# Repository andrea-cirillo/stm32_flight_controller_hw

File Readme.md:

<p align="center">
  <picture>
    <source media="(prefers-color-scheme: dark)" srcset="00%20-%20Docs/05%20-%20Brand/ACwing_logo_white.png">
    
  </picture>
</p>

<h1 align="center">ACwing – open drone flight hardware</h1>

<p align="center">
  STM32WB55 flight controller, 1S power board, GNSS and optical-flow expansions<br>
  KiCad 7 · JLCPCB-ready · by Andrea Cirillo
</p>

---

ACwing is a modular set of PCBs for small multirotors. The core is a **universal flight controller** that talks to its
power stage through the common **4-in-1 ESC connector** (JST SH 8-pin): on the 1S indoor mini drone it sits on the
ACwing 1S power board; on a larger 3S–6S brushless drone the same FC runs with one or two commercial 20 × 20 4-in-1
ESCs. Two optional expansion boards plug into the FC's **Qwiic** (I2C) ports: a **GNSS + compass** board for outdoor
flight and an **optical-flow + ToF** board for indoor position and height hold.

## Boards

| Board | Rev | Size | Layers | What it does | Docs | KiCad |
|---|---|---|---|---|---|---|
| **ACwing FC** | H | 40 × 40 mm, 20 × 20 holes (grommets) | 4, 1.0 mm | flight controller, 1S–6S input, up to 8 motors, BLE | [FC docs](00%20-%20Docs/00%20-%20FC_Docs/) | [project](01%20-%20FC_KiCadProj/) |
| **ACwing ESC 1S** | B | 40 × 40 mm, 20 × 20 holes | 4, 1.0 mm | 1S power board: 4 brushed motor stages, current sensor, USB-C charger | [ESC docs](00%20-%20Docs/01%20-%20ESC_1S_Docs/) | [project](02%20-%20ESC_1S_KiCadProj/) |
| **ACwing GPS** | D | 30 × 30 mm, 20 × 20 holes | 2, 1.0 mm | GNSS (u-blox SAM-M10Q) + compass, stacked above the FC | [GPS docs](00%20-%20Docs/02%20-%20GPS_Docs/) | [project](03%20-%20GPS_KiCadProj/) |
| **ACwing Flow** | A | 21 × 25 mm, 2 × M2 | 2, 1.0 mm | optical flow (PMW3901) + ToF height (VL53L1X), under the frame | [Flow docs](00%20-%20Docs/03%20-%20FLOW_Docs/) | [project](04%20-%20FLOW_KiCadProj/) |

Every board folder in `00 - Docs` holds the schematic PDF, the BoM with costing, the JLCPCB BoM and pick-and-place
files, the Gerber zip, the DRC report, the STEP model and board views.

## System

```
              ┌─────────────────────────┐   Qwiic (J3)   ┌──────────────────┐
              │      ACwing FC rev A    │───────────────▶│  ACwing GPS rev A │  optional, outdoor
  USB-C ─────▶│ STM32WB55 · IMU · baro  │                └──────────────────┘
  ELRS RX ───▶│ compass · 16 MB flash   │   Qwiic (J4)   ┌──────────────────┐
              │ BLE · 4 × RGB LED       │───────────────▶│ ACwing Flow rev A │  indoor
              └───────┬─────────┬───────┘                └──────────────────┘
          ESC link A  │         │  ESC link B (motors 5–8)
         (JST SH 8)   ▼         ▼
   ┌──────────────────────┐   ┌──────────────────────────┐
   │ ACwing ESC 1S rev A  │ or│ commercial 4-in-1 ESC(s) │
   │ 1S, brushed, charger │   │ 2S–6S, brushless         │
   └──────────────────────┘   └──────────────────────────┘
```

**Stack (1S mini drone, frame C2):** ESC 1S hard-mounted on the frame bosses → 5 mm → FC on M2 damping grommets →
6 mm → GPS board (optional). The flow board is mounted under the battery bay, sensor side down.

The interactive stack check (every part as a prism, every connector with a mated-plug envelope; 0 clashes) is in
[`04 - System_Docs/ACwing_stack_check.html`](00%20-%20Docs/04%20-%20System_Docs/) – download the folder and open the
page locally.

## Key features

**ACwing FC rev A**
- MCU **STM32WB55CGU6** (Cortex-M4 + M0+ radio core), BLE 5 with chip antenna and ST MLPF-WB55 front end.
- Sensors: **LSM6DSV16X** IMU, **LPS22HB** barometer, **IIS2MDC** compass; **W25Q128JV** 16 MB log flash.
- Input **1S–6S** (LM5166 buck, 3–65 V; 100 % duty cycle pass-through on 1S), 4.1 V system rail, 3.1 V and 3.31 V LDOs.
- **Two ESC links** (JST SH 8-pin, standard 4-in-1 pinout): 8 motor outputs (TIM2 / TIM1 / TIM16), VBAT and current
  sense from the ESC, battery pads for setups without a VBAT pin.
- Two Qwiic ports, ELRS / CRSF UART port, USB-C (data, DFU, bench supply), 4 × WS2812B, SWD pogo grid.

**ACwing ESC 1S rev A**
- 4 brushed motor stages (AON7524 N-MOSFETs) for coreless 8520 motors, 470 µF bulk capacitor.
- 2 mΩ shunt + TSC213 current sense (0.1 V/A) on the ESC link.
- USB-C 1S charger (STC4054, 455 mA) with a charge switch that keeps FC and motors off while charging.
- Battery solder pads for a JST PH 2.0 pigtail.

**ACwing GPS rev A** – u-blox **SAM-M10Q** (integrated patch antenna, I2C/DDC) and **IIS2MDC** compass away from the
motor currents; Qwiic in / out on the top side, PPS LED, backup supply.

**ACwing Flow rev A** – PixArt **PMW3901MB** flow sensor behind an **STM32C011** I2C bridge, ST **VL53L1X** ToF;
Qwiic in / out; all parts on the sensor side.

## Repository structure

```
00 - Docs/
├── 00 - FC_Docs/         FC rev A: README, pin map, schematic, BoM, JLC files, Gerber, STEP, views
├── 01 - ESC_1S_Docs/     ESC 1S rev A: same set
├── 02 - GPS_Docs/        GPS rev A: same set
├── 03 - FLOW_Docs/       Flow rev A: same set + mechanical DXF
├── 04 - System_Docs/     mechanical handoff, frame C2 answer and reply, stack check (3D page and render)
└── 05 - Brand/           ACwing logos (SVG/PNG), silkscreen logo footprints, brand and silkscreen tools
01 - FC_KiCadProj/        KiCad project, library, 3D models, generator scripts
02 - ESC_1S_KiCadProj/
03 - GPS_KiCadProj/
04 - FLOW_KiCadProj/
```

## Ordering (JLCPCB)

For each board, from its docs folder:
1. Upload `<board>_gerber.zip` (1.0 mm FR-4; 4 layers for FC and ESC, 2 layers for GPS and Flow).
2. Enable assembly and upload `<board>_BoM_JLCPCB.xlsx` and `<board>_CPL.xlsx`. Every BoM line carries its LCSC part
   number; the CPL already includes the rotation corrections. Check the pin-1 marks in the JLC preview as listed in the
   board README ("To check before ordering").

Indicative component cost per board (10 / 100 boards, components only): FC 28.2 / 22.7 USD, ESC 1S 6.4 / 5.1 USD,
GPS 27.6 / 23.4 USD, Flow 11.1 / 9.4 USD. Check LCSC stock before ordering.

## Status

**Layout update 2026-10-24 (still rev A):** FC microcontroller at the board centre, ESC link B next to the ELRS port on
the front edge, input buck moved to the left edge (no longer between the rear LEDs), LED supply kept away from the
magnetometer (EMI check in the FC README); GPS Qwiic J1 aligned with FC J3.

All four boards are routed with **0 DRC violations and 0 unconnected pads** (KiCad 7.0). They are not built and tested
yet: see each board README for the bench checks planned before the first order (ERC in KiCad 8/9, power-stage tests,
land patterns to verify). Firmware is a separate project.

## Author

**Andrea Cirillo** – ACwing hardware design.

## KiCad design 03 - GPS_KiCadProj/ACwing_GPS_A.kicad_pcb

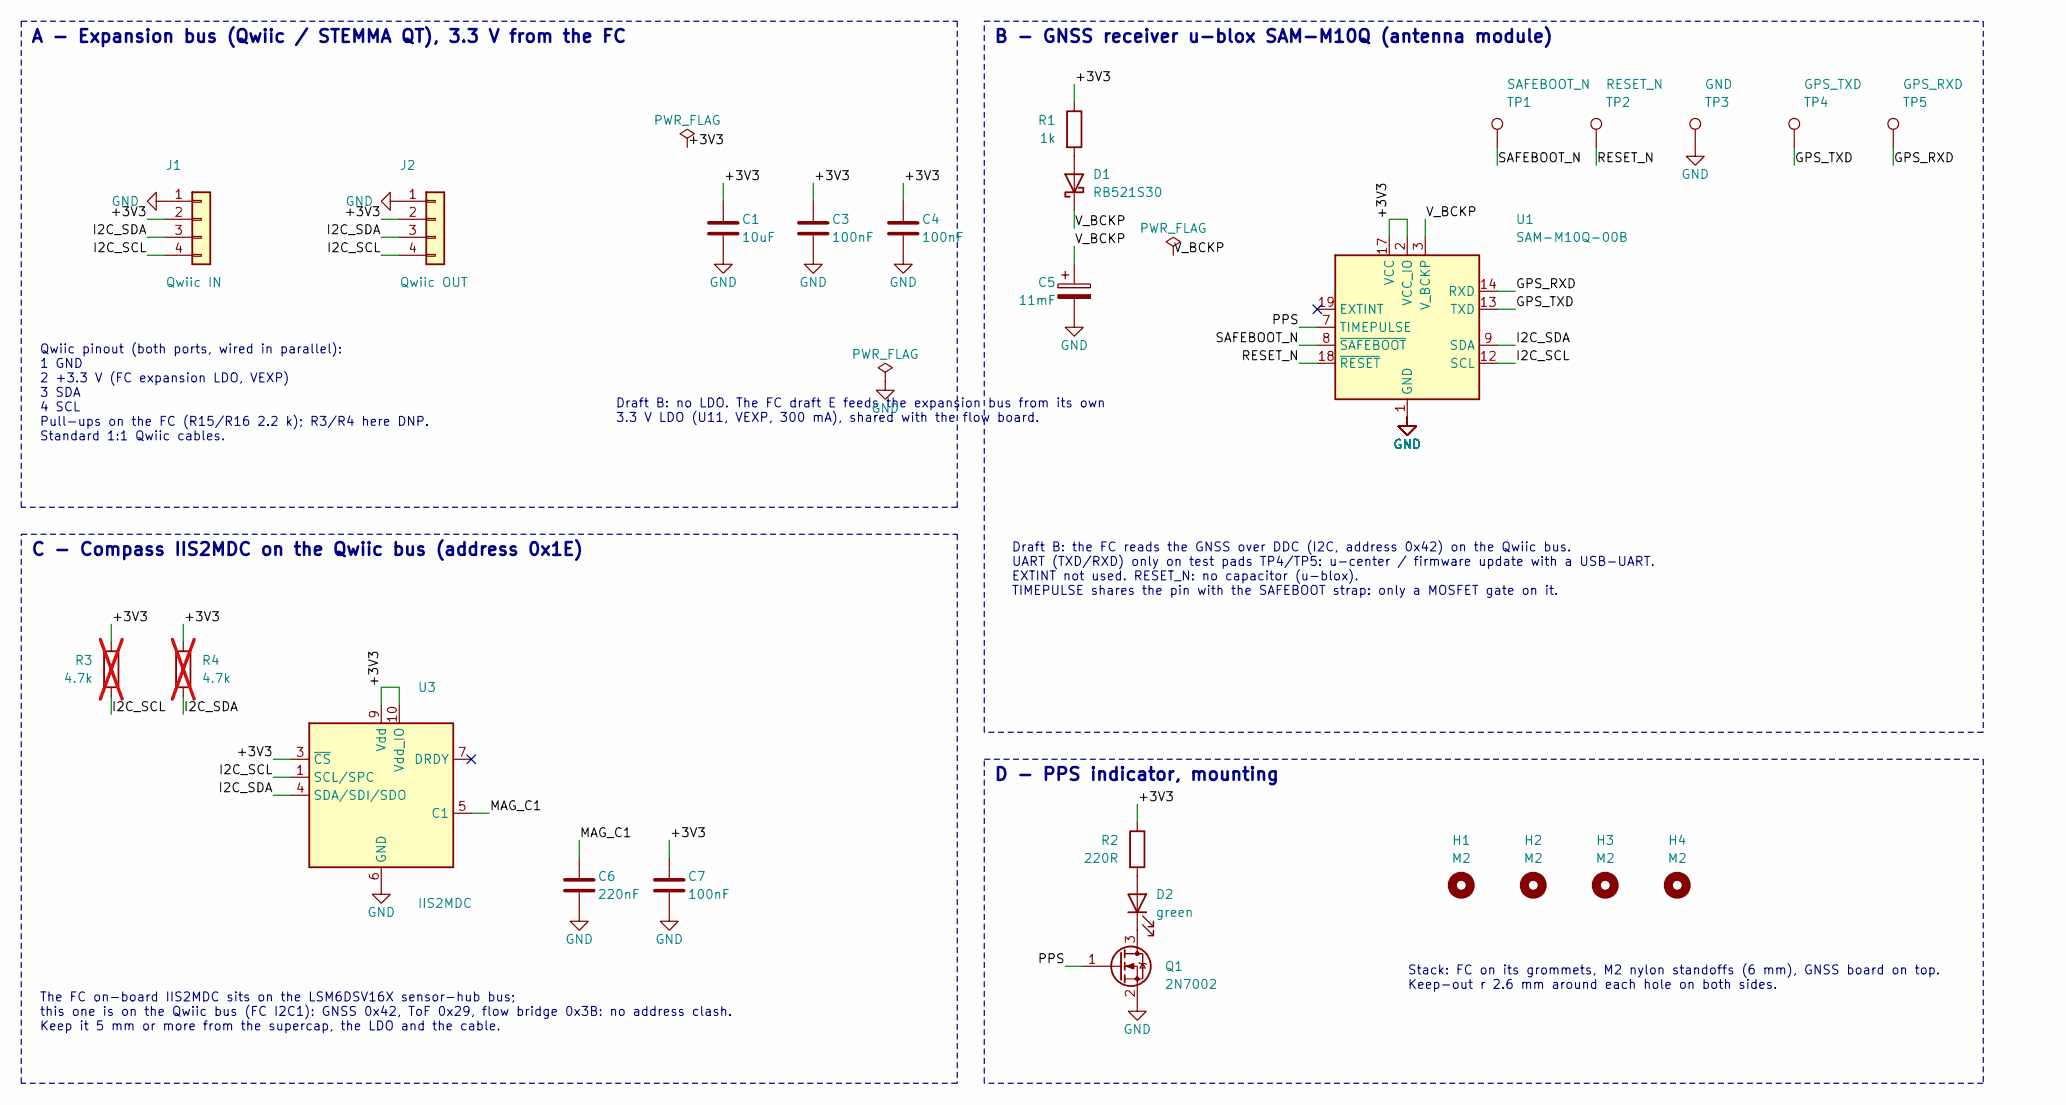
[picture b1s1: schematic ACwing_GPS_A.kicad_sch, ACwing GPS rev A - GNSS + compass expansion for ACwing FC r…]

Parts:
C1: 10uF; C_0603_1608Metric
C3, C4, C7: 100nF; C_0402_1005Metric
C5: 11mF; C_1210_3225Metric
C6: 220nF; C_0402_1005Metric
D1: RB521S30; D_SOD-523
D2: green; LED_0402_1005Metric
H1, H2, H3, H4: M2; MountingHole_2.2mm_M2
J1: Qwiic IN; JST_SH_SM04B-SRSS-TB_1x04-1MP_P1.00mm_Horizontal
J2: Qwiic OUT; JST_SH_SM04B-SRSS-TB_1x04-1MP_P1.00mm_Horizontal
Q1: 2N7002; SOT-23
R1: 1k; R_0402_1005Metric
R2: 220R; R_0402_1005Metric
R3, R4: 4.7k; R_0402_1005Metric; not fitted
TP1: SAFEBOOT_N; TestPoint_Pad_D1.0mm
TP2: RESET_N; TestPoint_Pad_D1.0mm
TP3: GND; TestPoint_Pad_D1.0mm
TP4: GPS_TXD; TestPoint_Pad_D1.0mm
TP5: GPS_RXD; TestPoint_Pad_D1.0mm
U1: SAM-M10Q-00B; ublox_SAM-M8Q
U3: IIS2MDC; LGA-12_2x2mm_P0.5mm

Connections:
+3V3: C1.1, C3.1, C4.1, C7.1, J1.2, J2.2, R1.1, R2.1, R3.1, R4.1, U1.2 (VCC_IO), U1.17 (VCC), U3.3 (~CS), U3.9 (Vdd), U3.10 (Vdd_IO)
GND: C1.2, C3.2, C4.2, C5.2, C6.2, C7.2, J1.1, J2.1, Q1.2 (S), TP3.1, U1.1 (GND), U1.4 (GND), U1.5 (GND), U1.6 (GND), U1.10 (GND), U1.11 (GND), U1.15 (GND), U1.16 (GND), U1.20 (GND), U3.6 (GND), U3.8 (GND)
GPS_RXD: TP5.1, U1.14 (RXD)
GPS_TXD: TP4.1, U1.13 (TXD)
I2C_SCL: J1.4, J2.4, R3.2, U1.12 (SCL), U3.1 (SCL/SPC)
I2C_SDA: J1.3, J2.3, R4.2, U1.9 (SDA), U3.4 (SDA/SDI/SDO)
MAG_C1: C6.1, U3.5 (C1)
unnamed: D1.2 (A), R1.2
unnamed: D2.2 (A), R2.2
unnamed: D2.1 (K), Q1.3 (D)
PPS: Q1.1 (G), U1.7 (TIMEPULSE)
RESET_N: TP2.1, U1.18 (~RESET)
SAFEBOOT_N: TP1.1, U1.8 (~SAFEBOOT)
V_BCKP: C5.1, D1.1 (K), U1.3 (V_BCKP)

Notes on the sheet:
A - Expansion bus (Qwiic / STEMMA QT), 3.3 V from the FC
Qwiic pinout (both ports, wired in parallel): 1 GND 2 +3.3 V (FC expansion LDO, VEXP) 3 SDA 4 SCL Pull-ups on the FC (R15/R16 2.2 k); R3/R4 here DNP. Standard 1:1 Qwiic cables.
Draft B: no LDO. The FC draft E feeds the expansion bus from its own 3.3 V LDO (U11, VEXP, 300 mA), shared with the flow board.
B - GNSS receiver u-blox SAM-M10Q (antenna module)
Draft B: the FC reads the GNSS over DDC (I2C, address 0x42) on the Qwiic bus. UART (TXD/RXD) only on test pads TP4/TP5: u-center / firmware update with a USB-UART. EXTINT not used. RESET_N: no capacitor (u-blox). TIMEPULSE shares the pin with the SAFEBOOT strap: only a MOSFET gate on it.
C - Compass IIS2MDC on the Qwiic bus (address 0x1E)
The FC on-board IIS2MDC sits on the LSM6DSV16X sensor-hub bus; this one is on the Qwiic bus (FC I2C1): GNSS 0x42, ToF 0x29, flow bridge 0x3B: no address clash. Keep it 5 mm or more from the supercap, the LDO and the cable.
D - PPS indicator, mounting
Stack: FC on its grommets, M2 nylon standoffs (6 mm), GNSS board on top. Keep-out r 2.6 mm around each hole on both sides.

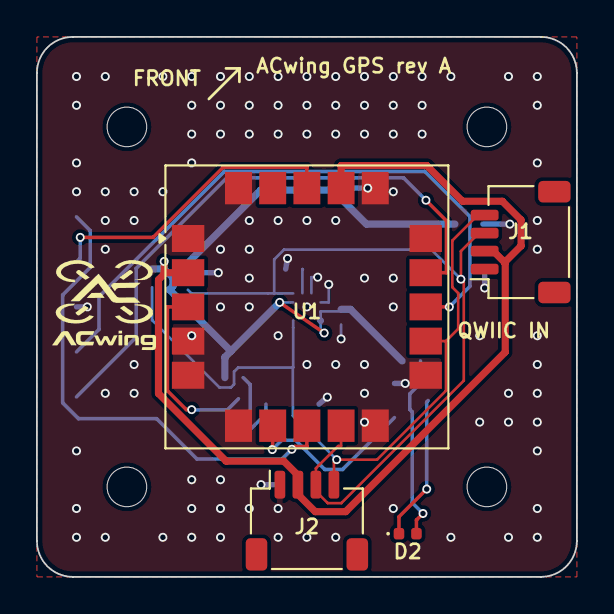
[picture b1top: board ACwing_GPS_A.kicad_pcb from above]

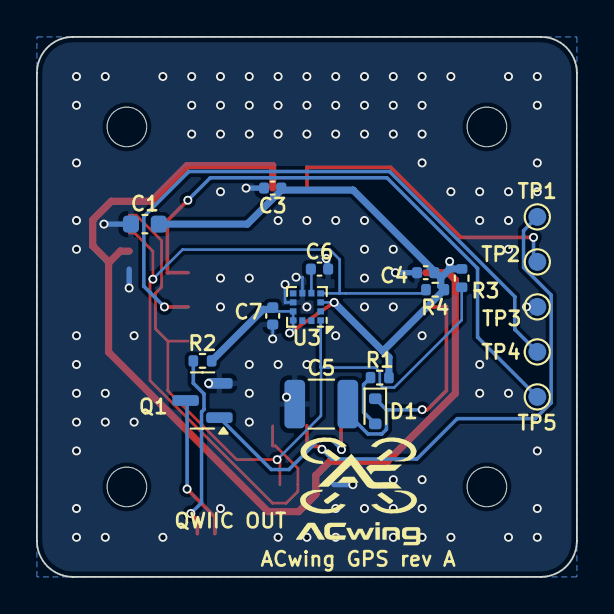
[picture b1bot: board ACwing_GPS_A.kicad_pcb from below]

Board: 2 copper layers, 30.0 x 30.0 mm, 28 parts (19 on the bottom side), 14 nets.

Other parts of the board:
LOGO1: ACwing_Logo_Full_5mm
LOGO2: ACwing_Logo_Full_6mm

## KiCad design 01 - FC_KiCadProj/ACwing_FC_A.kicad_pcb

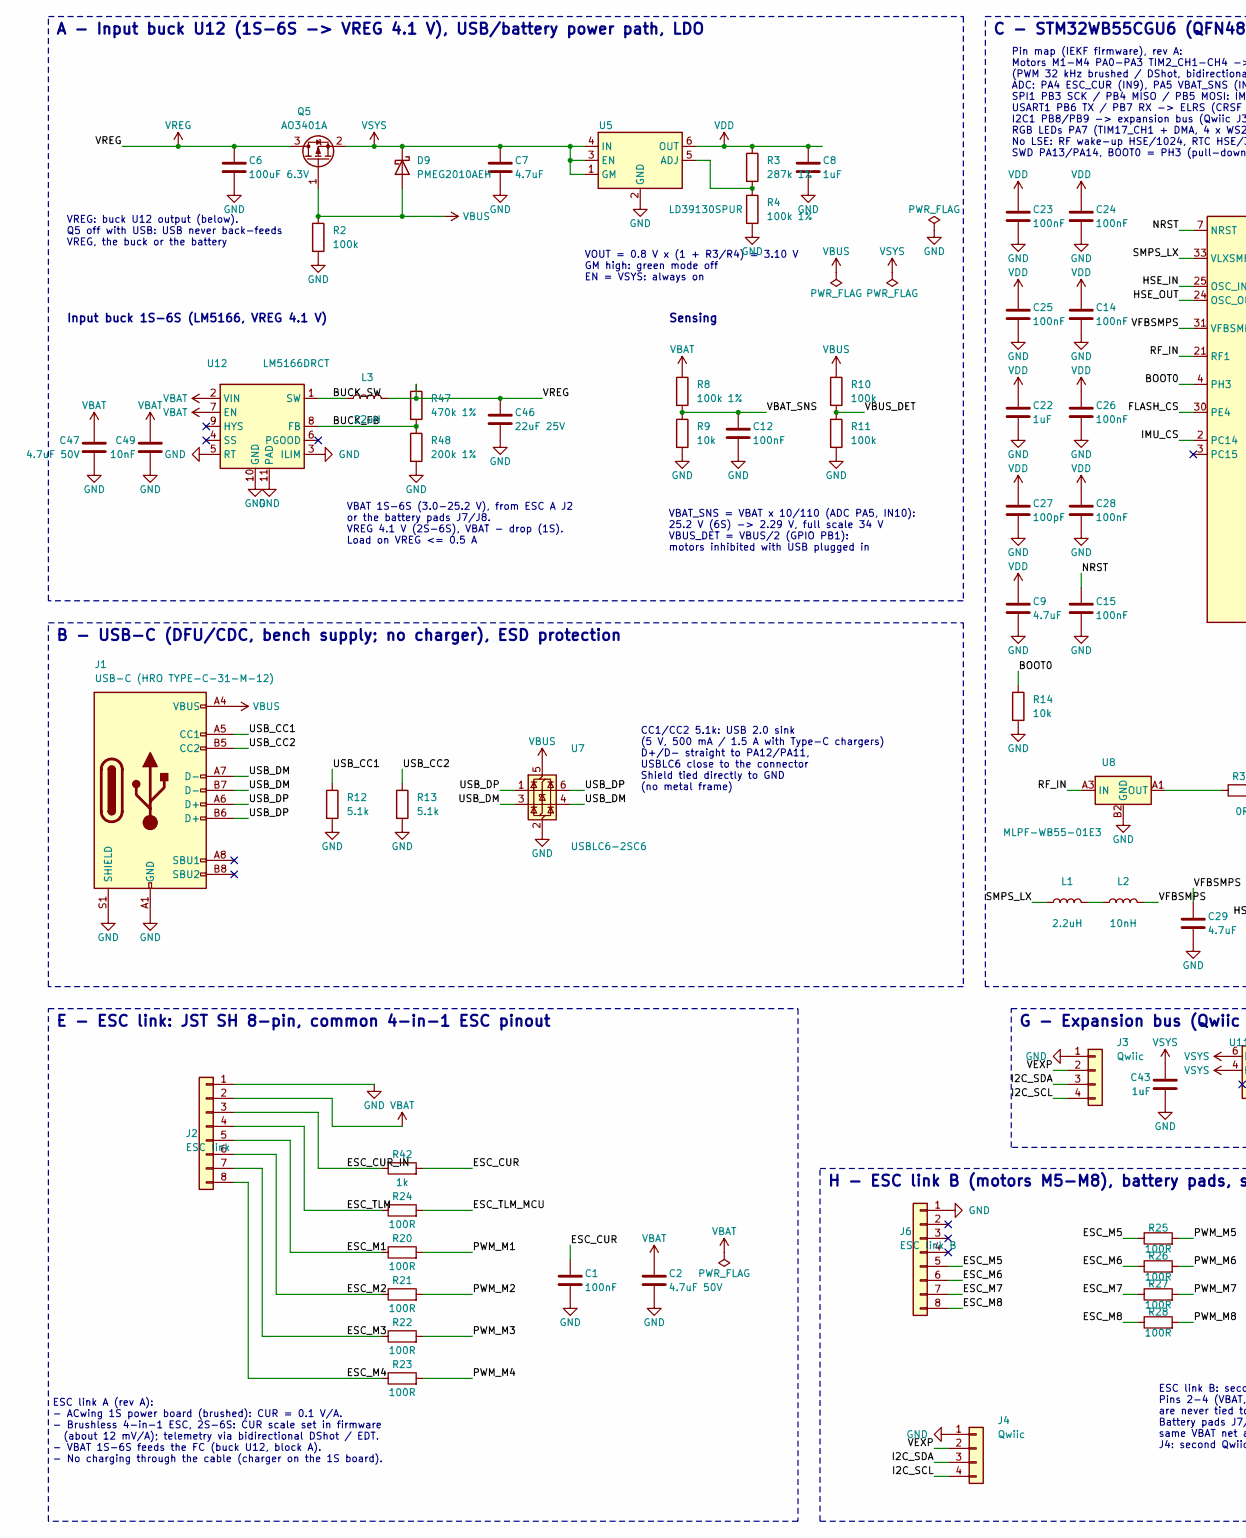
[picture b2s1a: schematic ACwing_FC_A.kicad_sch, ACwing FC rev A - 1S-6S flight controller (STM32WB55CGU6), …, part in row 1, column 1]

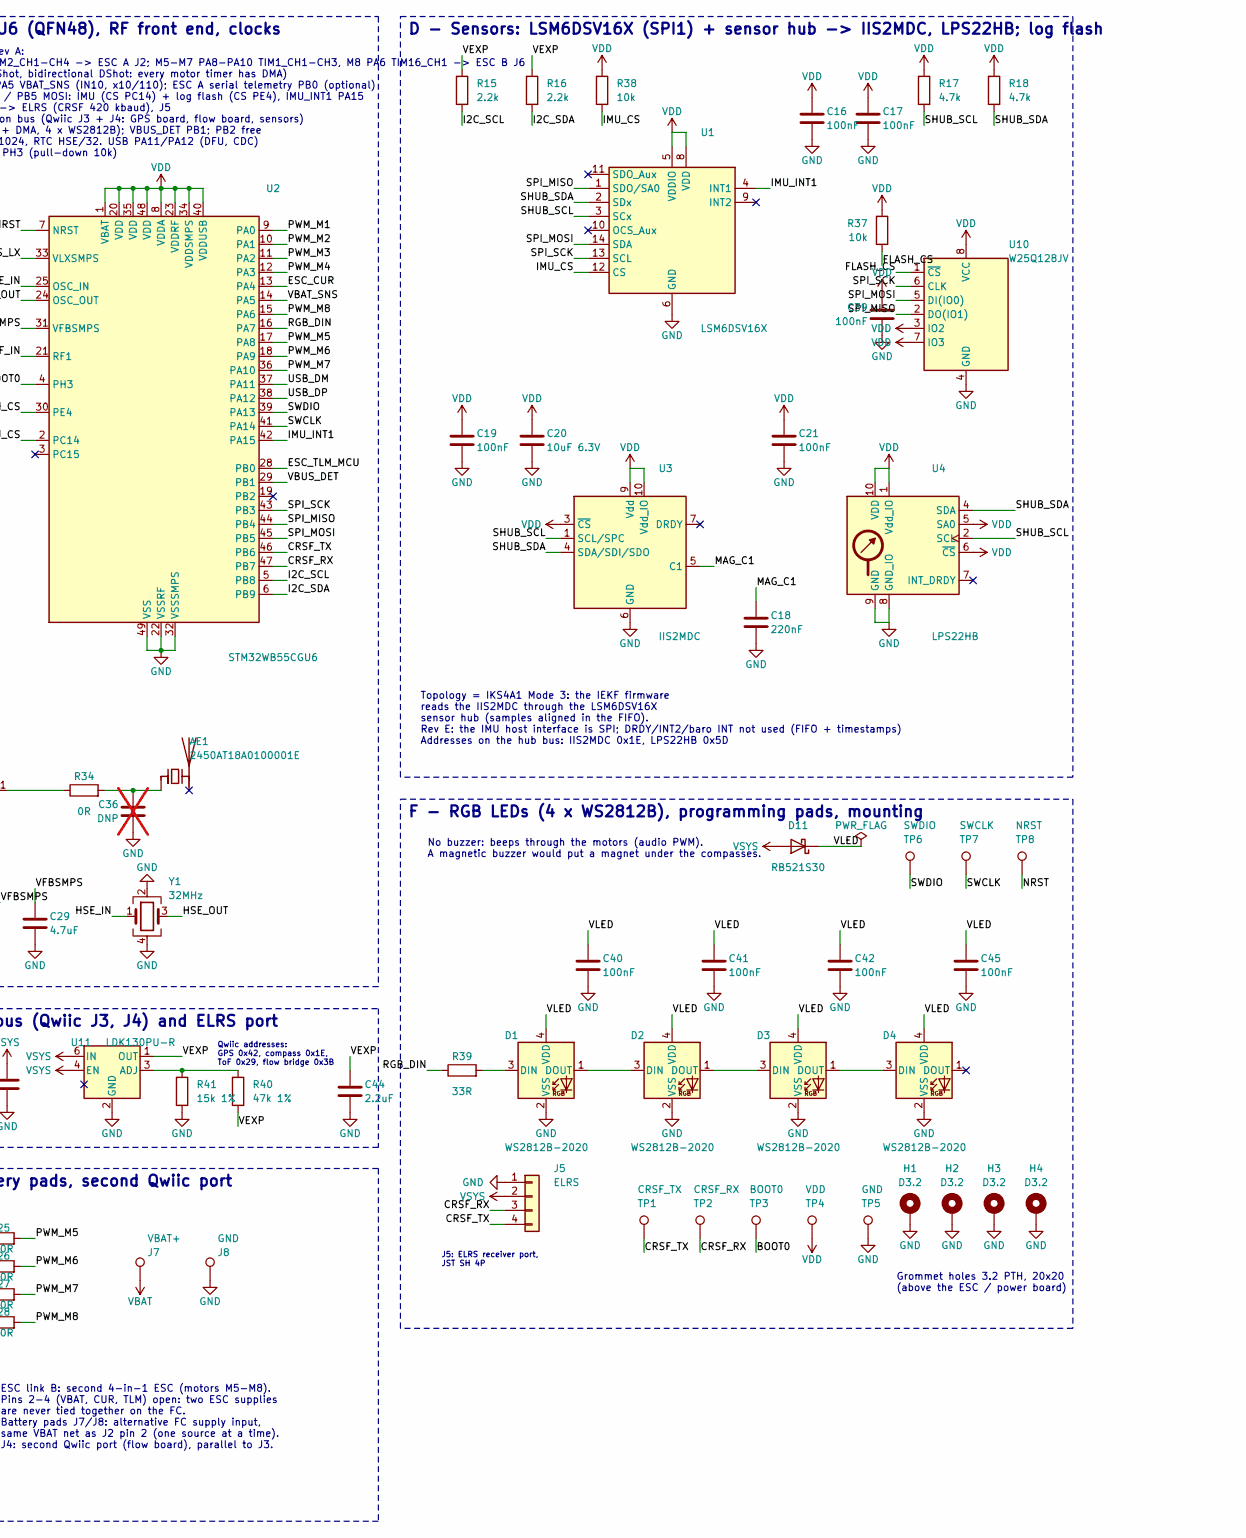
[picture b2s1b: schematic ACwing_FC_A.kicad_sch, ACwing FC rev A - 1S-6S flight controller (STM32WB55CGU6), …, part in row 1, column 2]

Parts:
AE1: 2450AT18A0100001E; Johanson_2450AT18x100
C1, C12, C14, C15, C16, C17, C19, C21, C23, C24, C25, C26, C28, C39, C40, C41, C42, C45: 100nF; C_0402_1005Metric
C2, C47: 4.7uF 50V; C_1206_3216Metric
C6: 100uF 6.3V; C_1206_3216Metric
C7, C9: 4.7uF; C_0603_1608Metric
C8, C22, C43: 1uF; C_0402_1005Metric
C18: 220nF; C_0402_1005Metric
C20: 10uF 6.3V; C_0603_1608Metric
C27: 100pF; C_0402_1005Metric
C29: 4.7uF; C_0402_1005Metric
C36: DNP; C_0402_1005Metric; not fitted
C44: 2.2uF; C_0402_1005Metric
C46: 22uF 25V; C_0805_2012Metric
C49: 10nF; C_0402_1005Metric
D1, D2, D3, D4: WS2812B-2020; LED_WS2812B-2020_PLCC4_2.0x2.0mm
D9: PMEG2010AEH; D_SOD-123F
D11: RB521S30; D_SOD-523
H1, H2, H3, H4: D3.2; Grommet_PTH_3.2mm_Pad5.0mm
J1: USB-C (HRO TYPE-C-31-M-12); USB_C_Receptacle_HRO_TYPE-C-31-M-12
J2: ESC link; JST_SH_SM08B-SRSS-TB_1x08-1MP_P1.00mm_Horizontal
J3, J4: Qwiic; JST_SH_SM04B-SRSS-TB_1x04-1MP_P1.00mm_Horizontal
J5: ELRS; JST_SH_SM04B-SRSS-TB_1x04-1MP_P1.00mm_Horizontal
J6: ESC link B; JST_SH_SM08B-SRSS-TB_1x08-1MP_P1.00mm_Horizontal
J7: VBAT+; TestPoint_Pad_2.0x2.0mm
J8: GND; TestPoint_Pad_2.0x2.0mm
L1: 2.2uH; L_0805_2012Metric
L2: 10nH; L_0402_1005Metric
L3: 22uH; L_Sunlord_SWPA5040S
Q5: AO3401A; SOT-23
R2, R10, R11: 100k; R_0402_1005Metric
R3: 287k 1%; R_0402_1005Metric
R4, R8: 100k 1%; R_0402_1005Metric
R9, R14, R37, R38: 10k; R_0402_1005Metric
R12, R13: 5.1k; R_0402_1005Metric
R15, R16: 2.2k; R_0402_1005Metric
R17, R18: 4.7k; R_0402_1005Metric
R20, R21, R22, R23, R24, R25, R26, R27, R28: 100R; R_0402_1005Metric
R34: 0R; R_0402_1005Metric
R39: 33R; R_0402_1005Metric
R40: 47k 1%; R_0402_1005Metric
R41: 15k 1%; R_0402_1005Metric
R42: 1k; R_0402_1005Metric
R47: 470k 1%; R_0402_1005Metric
R48: 200k 1%; R_0402_1005Metric
TP1: CRSF_TX; TestPoint_Pad_D1.0mm
TP2: CRSF_RX; TestPoint_Pad_D1.0mm
TP3: BOOT0; TestPoint_Pad_D1.0mm
TP4: VDD; TestPoint_Pad_D1.0mm
TP5: GND; TestPoint_Pad_D1.0mm
TP6: SWDIO; TestPoint_Pad_D1.0mm
TP7: SWCLK; TestPoint_Pad_D1.0mm
TP8: NRST; TestPoint_Pad_D1.0mm
U1: LSM6DSV16X; LGA-14_3x2.5mm_P0.5mm_LayoutBorder3x4y
U2: STM32WB55CGU6; QFN-48-1EP_7x7mm_P0.5mm_EP5.6x5.6mm
U3: IIS2MDC; LGA-12_2x2mm_P0.5mm
U4: LPS22HB; ST_HLGA-10_2x2mm_P0.5mm_LayoutBorder3x2y
U5: LD39130SPUR; DFN-6_1.3x1.2mm_P0.4mm
U7: USBLC6-2SC6; SOT-23-6
U8: MLPF-WB55-01E3; ST_MLPF-WB55-01E3_CSP-6
U10: W25Q128JV; WSON-8-1EP_6x5mm_P1.27mm_EP3.4x4mm
U11: LDK130PU-R; DFN-6_1.3x1.2mm_P0.4mm
U12: LM5166DRCT; Texas_DRC0010J
Y1: 32MHz; Crystal_SMD_2016-4Pin_2.0x1.6mm

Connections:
BOOT0: R14.1, TP3.1, U2.4 (PH3)
BUCK_FB: R47.2, R48.1, U12.8 (FB)
BUCK_SW: L3.1, U12.1 (SW)
CRSF_RX: J5.3, TP2.1, U2.47 (PB7)
CRSF_TX: J5.4, TP1.1, U2.46 (PB6)
ESC_CUR: C1.1, R42.2, U2.13 (PA4)
ESC_CUR_IN: J2.3, R42.1
ESC_M1: J2.5, R20.1
ESC_M2: J2.6, R21.1
ESC_M3: J2.7, R22.1
ESC_M4: J2.8, R23.1
ESC_M5: J6.5, R25.1
ESC_M6: J6.6, R26.1
ESC_M7: J6.7, R27.1
ESC_M8: J6.8, R28.1
ESC_TLM: J2.4, R24.1
ESC_TLM_MCU: R24.2, U2.28 (PB0)
FLASH_CS: R37.2, U2.30 (PE4), U10.1 (~CS)
GND: C1.2, C2.2, C6.2, C7.2, C8.2, C9.2, C12.2, C14.2, C15.2, C16.2, C17.2, C18.2, C19.2, C20.2, C21.2, C22.2, C23.2, C24.2, C25.2, C26.2, C27.2, C28.2, C29.2, C36.2, C39.2, C40.2, C41.2, C42.2, C43.2, C44.2, C45.2, C46.2, C47.2, C49.2, D1.2 (VSS), D2.2 (VSS), D3.2 (VSS), D4.2 (VSS), H1.1, H2.1, H3.1, H4.1, J1.A1 (GND), J1.A12 (GND), J1.B1 (GND), J1.B12 (GND), J1.S1 (SHIELD), J2.1, J3.1, J4.1, J5.1, J6.1, J8.1, R2.2, R4.2, R9.2, R11.2, R12.2, R13.2, R14.2, R41.2, R48.2, TP5.1, U1.6 (GND), U1.7 (GND), U2.22 (VSSRF), U2.32 (VSSSMPS), U2.49 (VSS), U3.6 (GND), U3.8 (GND), U4.3 (GND), U4.8 (GND_IO), U4.9 (GND), U5.2 (GND), U7.2 (GND), U8.A2 (GND), U8.B1 (GND), U8.B2 (GND), U8.B3 (GND), U10.4 (GND), U11.2 (GND), U12.3 (ILIM), U12.5 (RT), U12.10 (GND), U12.11 (PAD), Y1.2, Y1.4
HSE_IN: U2.25 (OSC_IN), Y1.1
HSE_OUT: U2.24 (OSC_OUT), Y1.3
I2C_SCL: J3.4, J4.4, R15.2, U2.5 (PB8)
I2C_SDA: J3.3, J4.3, R16.2, U2.6 (PB9)
IMU_CS: R38.2, U1.12 (CS), U2.2 (PC14)
IMU_INT1: U1.4 (INT1), U2.42 (PA15)
MAG_C1: C18.1, U3.5 (C1)
NRST: C15.1, TP8.1, U2.7 (NRST)
unnamed: AE1.1 (FEED), C36.1, R34.2
unnamed: D1.3 (DIN), R39.2
unnamed: D1.1 (DOUT), D2.3 (DIN)
unnamed: D2.1 (DOUT), D3.3 (DIN)
unnamed: D3.1 (DOUT), D4.3 (DIN)
unnamed: L1.2, L2.1
unnamed: R3.2, R4.1, U5.5 (ADJ)
unnamed: R34.1, U8.A1 (OUT)
unnamed: R40.1, R41.1, U11.3 (ADJ)
PWM_M1: R20.2, U2.9 (PA0)
PWM_M2: R21.2, U2.10 (PA1)
PWM_M3: R22.2, U2.11 (PA2)
PWM_M4: R23.2, U2.12 (PA3)
PWM_M5: R25.2, U2.17 (PA8)
PWM_M6: R26.2, U2.18 (PA9)
PWM_M7: R27.2, U2.36 (PA10)
PWM_M8: R28.2, U2.15 (PA6)
RF_IN: U2.21 (RF1), U8.A3 (IN)
RGB_DIN: R39.1, U2.16 (PA7)
SHUB_SCL: R17.2, U1.3 (SCx), U3.1 (SCL/SPC), U4.2 (SCL)
SHUB_SDA: R18.2, U1.2 (SDx), U3.4 (SDA/SDI/SDO), U4.4 (SDA)
SMPS_LX: L1.1, U2.33 (VLXSMPS)
SPI_MISO: U1.1 (SDO/SA0), U2.44 (PB4), U10.2 (DO(IO1))
SPI_MOSI: U1.14 (SDA), U2.45 (PB5), U10.5 (DI(IO0))
SPI_SCK: U1.13 (SCL), U2.43 (PB3), U10.6 (CLK)
SWCLK: TP7.1, U2.41 (PA14)
SWDIO: TP6.1, U2.39 (PA13)
USB_CC1: J1.A5 (CC1), R12.1
USB_CC2: J1.B5 (CC2), R13.1
USB_DM: J1.A7 (D-), J1.B7 (D-), U2.37 (PA11), U7.3 (I/O2), U7.4 (I/O2)
USB_DP: J1.A6 (D+), J1.B6 (D+), U2.38 (PA12), U7.1 (I/O1), U7.6 (I/O1)
VBAT: C2.1, C47.1, C49.1, J2.2, J7.1, R8.1, U12.2 (VIN), U12.7 (EN)
VBAT_SNS: C12.1, R8.2, R9.1, U2.14 (PA5)
VBUS: D9.2 (A), J1.A4 (VBUS), J1.A9 (VBUS), J1.B4 (VBUS), J1.B9 (VBUS), Q5.1 (G), R2.1, R10.1, U7.5 (VBUS)
VBUS_DET: R10.2, R11.1, U2.29 (PB1)
VDD: C8.1, C9.1, C14.1, C16.1, C17.1, C19.1, C20.1, C21.1, C22.1, C23.1, C24.1, C25.1, C26.1, C27.1, C28.1, C39.1, R3.1, R17.1, R18.1, R37.1, R38.1, TP4.1, U1.5 (VDDIO), U1.8 (VDD), U2.1 (VBAT), U2.8 (VDDA), U2.20 (VDD), U2.23 (VDDRF), U2.34 (VDDSMPS), U2.35 (VDD), U2.40 (VDDUSB), U2.48 (VDD), U3.3 (~CS), U3.9 (Vdd), U3.10 (Vdd_IO), U4.1 (Vdd_IO), U4.5 (SA0), U4.6 (~CS), U4.10 (VDD), U5.6 (OUT), U10.3 (IO2), U10.7 (IO3), U10.8 (VCC)
VEXP: C44.1, J3.2, J4.2, R15.1, R16.1, R40.2, U11.1 (OUT)
VFBSMPS: C29.1, L2.2, U2.31 (VFBSMPS)
VLED: C40.1, C41.1, C42.1, C45.1, D1.4 (VDD), D2.4 (VDD), D3.4 (VDD), D4.4 (VDD), D11.1 (K)
VREG: C6.1, C46.1, L3.2, Q5.3 (D), R47.1
VSYS: C7.1, C43.1, D9.1 (K), D11.2 (A), J5.2, Q5.2 (S), U5.1 (GM), U5.3 (EN), U5.4 (IN), U11.4 (EN), U11.6 (IN)

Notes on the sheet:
A - Input buck U12 (1S-6S -> VREG 4.1 V), USB/battery power path, LDO
VOUT = 0.8 V x (1 + R3/R4) = 3.10 V GM high: green mode off EN = VSYS: always on
VREG: buck U12 output (below). Q5 off with USB: USB never back-feeds VREG, the buck or the battery
Input buck 1S-6S (LM5166, VREG 4.1 V)
VBAT 1S-6S (3.0-25.2 V), from ESC A J2 or the battery pads J7/J8. VREG 4.1 V (2S-6S), VBAT - drop (1S). Load on VREG <= 0.5 A
Sensing
VBAT_SNS = VBAT x 10/110 (ADC PA5, IN10): 25.2 V (6S) -> 2.29 V, full scale 34 V VBUS_DET = VBUS/2 (GPIO PB1): motors inhibited with USB plugged in
B - USB-C (DFU/CDC, bench supply; no charger), ESD protection
CC1/CC2 5.1k: USB 2.0 sink (5 V, 500 mA / 1.5 A with Type-C chargers) D+/D- straight to PA12/PA11, USBLC6 close to the connector Shield tied directly to GND (no metal frame)
C - STM32WB55CGU6 (QFN48), RF front end, clocks
Pin map (IEKF firmware), rev A: Motors M1-M4 PA0-PA3 TIM2_CH1-CH4 -> ESC A J2; M5-M7 PA8-PA10 TIM1_CH1-CH3, M8 PA6 TIM16_CH1 -> ESC B J6 (PWM 32 kHz brushed / DShot, bidirectional DShot: every motor timer has DMA) ADC: PA4 ESC_CUR (IN9), PA5 VBAT_SNS (IN10, x10/110); ESC A serial telemetry PB0 (opt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
D - Sensors: LSM6DSV16X (SPI1) + sensor hub -> IIS2MDC, LPS22HB; log flash
Topology = IKS4A1 Mode 3: the IEKF firmware reads the IIS2MDC through the LSM6DSV16X sensor hub (samples aligned in the FIFO). Rev E: the IMU host interface is SPI; DRDY/INT2/baro INT not used (FIFO + timestamps) Addresses on the hub bus: IIS2MDC 0x1E, LPS22HB 0x5D
E - ESC link: JST SH 8-pin, common 4-in-1 ESC pinout
ESC link A (rev A): - ACwing 1S power board (brushed): CUR = 0.1 V/A. - Brushless 4-in-1 ESC, 2S-6S: CUR scale set in firmware (about 12 mV/A); telemetry via bidirectional DShot / EDT. - VBAT 1S-6S feeds the FC (buck U12, block A). - No charging through the cable (charger on the 1S board).
H - ESC link B (motors M5-M8), battery pads, second Qwiic port
ESC link B: second 4-in-1 ESC (motors M5-M8). Pins 2-4 (VBAT, CUR, TLM) open: two ESC supplies are never tied together on the FC. Battery pads J7/J8: alternative FC supply input, same VBAT net as J2 pin 2 (one source at a time). J4: second Qwiic port (flow board), parallel to J3.
F - RGB LEDs (4 x WS2812B), programming pads, mounting
No buzzer: beeps through the motors (audio PWM). A magnetic buzzer would put a magnet under the compasses.
Grommet holes 3.2 PTH, 20x20 (above the ESC / power board)
G - Expansion bus (Qwiic J3, J4) and ELRS port
J5: ELRS receiver port, JST SH 4P
Qwiic addresses: GPS 0x42, compass 0x1E, ToF 0x29, flow bridge 0x3B

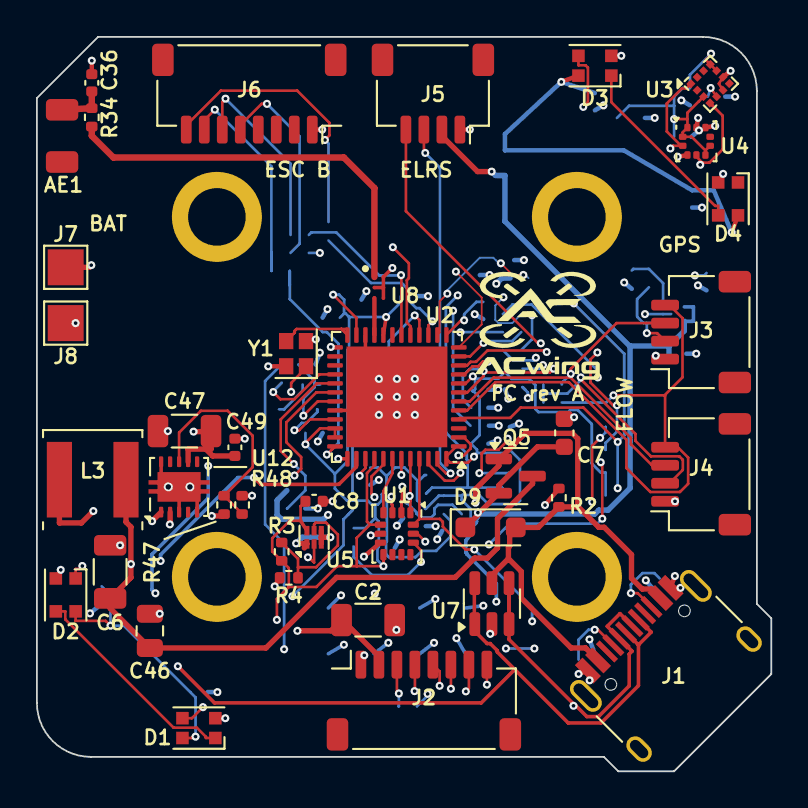
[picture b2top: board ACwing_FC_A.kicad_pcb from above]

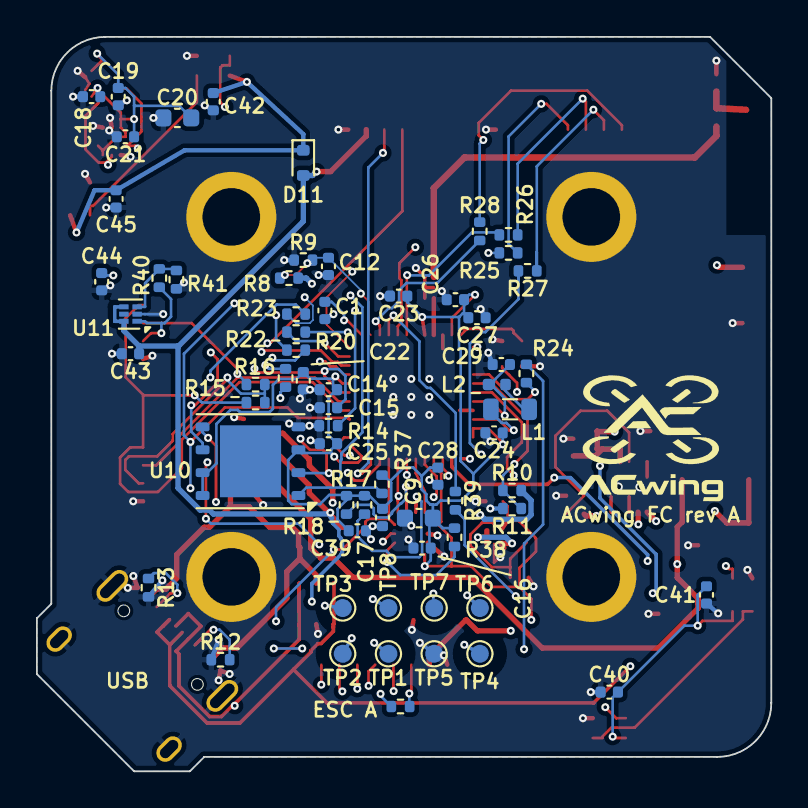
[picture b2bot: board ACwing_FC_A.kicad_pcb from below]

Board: 4 copper layers, 40.8 x 40.8 mm, 110 parts (66 on the bottom side), 68 nets.

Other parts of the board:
LOGO1: ACwing_Logo_Full_6mm
LOGO2: ACwing_Logo_Full_7mm

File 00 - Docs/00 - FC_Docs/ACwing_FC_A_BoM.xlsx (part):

ACwing FC rev A - assembly BoM (1 board)
Source: ACwing_FC_A.kicad_sch / ACwing_FC_A.kicad_pcb. MPNs = parts as assemble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
Item | Quantity | Part Reference | Value | MPN | Manufacturer | LCSC / JLCPCB # | Package | Description | Side | Notes
1 | 1 | AE1 | 2450AT18A0100001E | 2450AT18A0100001E | Johanson Technology | C17430588 | 1206 (3.2 x 1.6 x 1.3 mm) | Chip antenna, 2.4 GHz, 0.5 dBi, 50 Ohm | Top | Johanson global P/N of the legacy 2450AT18A100E (same part). Left board edge, i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
2 | 18 | C1, C12, C14, C15, C16, C17, C19, C21, C23, C24, C25, C26, C28, C39, C40, C41, 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 | 100nF | CL05B104KO5NNNC | Samsung Electro-Mechanics | C1525 | 0402 (1005 metric) | Capacitor, MLCC, 100 nF, 16 V, X7R, 10% | Bottom | Decoupling (MCU, sensors, NRST). JLC Basic part (replaces Murata GRM155R71C104K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
3 | 2 | C2, C47 | 4.7uF 50V | 1206B475K500NT | FH (Guangdong Fenghua) | C29823 | 1206 (3216 metric), h 1.6 mm | Capacitor, MLCC, 4.7 uF, 50 V, X7R, 10% | Top | VBAT (up to 6S): buck input (C47), ESC link A (C2). JLC Basic part
4 | 1 | C6 | 100uF 6.3V | CL31A107MQHNNNE | Samsung Electro-Mechanics | C15008 | 1206 (3216 metric), h 1.6 mm | Capacitor, MLCC, 100 uF, 6.3 V, X5R, 20% | Top | Buck output (VREG). Replaces Murata GRM31CR60J107ME39L
5 | 1 | C7 | 4.7uF | CL10A475KO8NNNC | Samsung Electro-Mechanics | C19666 | 0603 (1608 metric), h 0.8 mm | Capacitor, MLCC, 4.7 uF, 16 V, X5R, 10% | Top | VSYS (C7) and MCU VDD bulk (C9). JLC Basic part, 16 V rating (replaces Murata G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
6 | 1 | C8 | 1uF | CL05A105KA5NQNC | Samsung Electro-Mechanics | C52923 | 0402 (1005 metric) | Capacitor, MLCC, 1 uF, 25 V, X5R, 10% | Top | LDO output (C8), VDDA (C22). JLC Basic part (replaces Murata GRM155R61A105KE15D)
7 | 1 | C9 | 4.7uF | CL10A475KO8NNNC | Samsung Electro-Mechanics | C19666 | 0603 (1608 metric), h 0.8 mm | Capacitor, MLCC, 4.7 uF, 16 V, X5R, 10% | Bottom | VSYS (C7) and MCU VDD bulk (C9). JLC Basic part, 16 V rating (replaces Murata G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
8 | 1 | C18 | 220nF | CL05B224KO5NNNC | Samsung Electro-Mechanics | C16772 | 0402 (1005 metric) | Capacitor, MLCC, 220 nF, 16 V, X7R, 10% | Bottom | IIS2MDC C1 (ESR < 200 mOhm). Replaces Murata GRM155R71C224KA12D
9 | 1 | C20 | 10uF 6.3V | CL10A106KP8NNNC | Samsung Electro-Mechanics | C19702 | 0603 (1608 metric), h 0.8 mm | Capacitor, MLCC, 10 uF, 10 V, X5R, 10% | Bottom | VDD bulk, bottom side. JLC Basic part, 10 V rating (replaces Murata GRM188R60J1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
10 | 2 | C22, C43 | 1uF | CL05A105KA5NQNC | Samsung Electro-Mechanics | C52923 | 0402 (1005 metric) | Capacitor, MLCC, 1 uF, 25 V, X5R, 10% | Bottom | LDO output (C8), VDDA (C22). JLC Basic part (replaces Murata GRM155R61A105KE15D)
11 | 1 | C27 | 100pF | 0402CG101J500NT | FH (Guangdong Fenghua) | C1546 | 0402 (1005 metric) | Capacitor, MLCC, 100 pF, 50 V, C0G, 5% | Bottom | VDDRF high-frequency decoupling. JLC Basic part (replaces Murata GRM1555C1H101J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
12 | 1 | C29 | 4.7uF | CL05A475MP5NRNC | Samsung Electro-Mechanics | C23733 | 0402 (1005 metric) | Capacitor, MLCC, 4.7 uF, 10 V, X5R, 20% | Bottom | SMPS output (VFBSMPS). Replaces Murata GRM155R61A475MEAAD
13 | 1 | C44 | 2.2uF | CL05A225MQ5NSNC | Samsung Electro-Mechanics | C12530 | 0402 (1005 metric) | Capacitor, MLCC, 2.2 uF, 6.3 V, X5R, 20% | Bottom | Expansion LDO output (VEXP). JLC Basic part
14 | 1 | C46 | 22uF 25V | CL21A226MAQNNNE | Samsung Electro-Mechanics | C45783 | 0805 (2012 metric), h 1.25 mm | Capacitor, MLCC, 22 uF, 25 V, X5R, 20% | Top | Buck output (with C6). JLC Basic part
15 | 1 | C49 | 10nF | CL05B103KB5NNNC | Samsung Electro-Mechanics | C15195 | 0402 (1005 metric) | Capacitor, MLCC, 10 nF, 50 V, X7R, 10% | Top | -. JLC Basic part
16 | 4 | D1, D2, D3, D4 | WS2812B-2020 | WS2812B-2020 | Worldsemi | C965555 | 2.0 x 2.0 x 0.84 mm, 4 pad | LED, RGB addressable, integrated driver, 2.0 x 2.0 mm | Top | Status LEDs D1 rear, D2 left, D3 front, D4 right: one chain from PA7 (TIM17_CH1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
17 | 1 | D9 | PMEG2010AEH | PMEG2010AEH,115 | Nexperia | C110921 | SOD-123F | Diode, Schottky, 20 V, 1 A, Vf ~0.35 V | Top | USB VBUS -> VSYS
18 | 1 | D11 | RB521S30 | RB521S30T1G | onsemi | C8523 | SOD-523 | Diode, Schottky, 30 V, 200 mA, SOD-523 | Bottom | VSYS -> VLED (keeps the LEDs below their VDD max with USB 5 V)
19 | 1 | J1 | USB-C (HRO TYPE-C-31-M-12) | TYPE-C-31-M-12 | HRO (Korea Hroparts) | C165948 | USB-C receptacle, 16 pin, SMD + THT shell | Connector, USB Type-C receptacle, USB 2.0, top mount | Top | Mouth 0.35 mm past the right-corner chamfer
20 | 1 | J2 | ESC link | SM08B-SRSS-TB(LF)(SN) | JST | C160407 | JST SH 8P side entry, h 2.9 mm | Connector, JST SH, 8 positions, 1.0 mm pitch, side entry | Top | ESC links (top side): J2 ESC A rear edge (power, CUR, M1-M4); J6 ESC B front ed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
21 | 2 | J3, J4 | Qwiic | SM04B-SRSS-TB(LF)(SN) | JST | C160404 | JST SH 4P side entry, SMD, h 2.9 mm | Connector, JST SH, 4 positions, 1.0 mm pitch, side entry, SMD | Top | Qwiic / STEMMA QT expansion port (GPS, flow): 1 GND, 2 3.3 V, 3 SDA, 4 SCL. Qwi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
22 | 1 | J5 | ELRS | SM04B-SRSS-TB(LF)(SN) | JST | C160404 | JST SH 4P side entry, SMD, h 2.9 mm | Connector, JST SH, 4 positions, 1.0 mm pitch, side entry, SMD | Top | ELRS receiver port (CRSF, USART1): 1 GND, 2 VSYS, 3 RX, 4 TX. ELRS receiver por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
23 | 1 | J6 | ESC link B | SM08B-SRSS-TB(LF)(SN) | JST | C160407 | JST SH 8P side entry, h 2.9 mm | Connector, JST SH, 8 positions, 1.0 mm pitch, side entry | Top | ESC link B (M5-M8), top side, front edge next to the ELRS port J5, mouth toward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
24 | 1 | L1 | 2.2uH | MPH201210S2R2MT | Sunlord | C55755 | 0805 (2012 metric), h 1.0 mm | Inductor, multilayer power, 2.2 uH, 20%, 420 mA, DCR 0.25 Ohm, 2.0 x 1.2 x 1.0 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 | Bottom | SMPS inductor for the 8 MHz SMPS clock (DS13252 table 6). SMPS inductor, 8 MHz 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
25 | 1 | L2 | 10nH | LQG15HS10NJ02D | Murata | C77103 | 0402 (1005 metric) | Inductor, multilayer, 10 nH, 5%, 500 mA | Bottom | SMPS output filter, AN5290. Replaces LQG15WZ10NJ02D (same value, LCSC stocked)
26 | 1 | L3 | 22uH | SWPA5040S220MT | Sunlord | C68434 | SMD 5 x 5 x 4 mm, shielded | Inductor, shielded power, 22 uH, 20%, Irated 1.5 A, Isat 1.9 A, DCR 168 mOhm, 5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 | Top | Input buck inductor (top, left edge, ~41 mm from the magnetometer)
27 | 1 | Q5 | AO3401A | AO3401A | Alpha & Omega Semiconductor | C15127 | SOT-23 | MOSFET, P-channel, 30 V, 4 A | Top | Battery/USB load sharing
28 | 1 | R2 | 100k | 0402WGF1003TCE | UNI-ROYAL | C25741 | 0402 (1005 metric) | Resistor, 100 kOhm, 1%, 1/16 W | Top | Q5 gate pull-down (R2), VBUS sense divider (R10, R11). JLC Basic part
29 | 1 | R3 | 287k 1% | RC-02K2873FT | FH (Guangdong Fenghua) | C42921050 | 0402 (1005 metric) | Resistor, 287 kOhm, 1%, 1/16 W | Top | LDO feedback (VOUT = 3.10 V)
30 | 1 | R4 | 100k 1% | 0402WGF1003TCE | UNI-ROYAL | C25741 | 0402 (1005 metric) | Resistor, 100 kOhm, 1%, 1/16 W | Top | LDO feedback (R4), VBAT sense divider top (R8). JLC Basic part
31 | 1 | R8 | 100k 1% | 0402WGF1003TCE | UNI-ROYAL | C25741 | 0402 (1005 metric) | Resistor, 100 kOhm, 1%, 1/16 W | Bottom | LDO feedback (R4), VBAT sense divider top (R8). JLC Basic part
32 | 4 | R9, R14, R37, R38 | 10k | 0402WGF1002TCE | UNI-ROYAL | C25744 | 0402 (1005 metric) | Resistor, 10 kOhm, 1%, 1/16 W | Bottom | BOOT0 pull-down (R14), FLASH_CS / IMU_CS pull-ups (R37, R38), VBAT sense divide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
33 | 2 | R10, R11 | 100k | 0402WGF1003TCE | UNI-ROYAL | C25741 | 0402 (1005 metric) | Resistor, 100 kOhm, 1%, 1/16 W | Bottom | Q5 gate pull-down (R2), VBUS sense divider (R10, R11). JLC Basic part
34 | 2 | R12, R13 | 5.1k | 0402WGF5101TCE | UNI-ROYAL | C25905 | 0402 (1005 metric) | Resistor, 5.1 kOhm, 1%, 1/16 W | Bottom | USB-C CC pull-downs. JLC Basic part
35 | 2 | R15, R16 | 2.2k | 0402WGF2201TCE | UNI-ROYAL | C25879 | 0402 (1005 metric) | Resistor, 2.2 kOhm, 1%, 1/16 W | Bottom | I2C1 pull-ups. JLC Basic part
36 | 2 | R17, R18 | 4.7k | 0402WGF4701TCE | UNI-ROYAL | C25900 | 0402 (1005 metric) | Resistor, 4.7 kOhm, 1%, 1/16 W | Bottom | Sensor hub pull-ups. JLC Basic part
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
